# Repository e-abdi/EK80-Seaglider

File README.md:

# EK80 Seaglider

Integration of a Simrad EK80 echosounder on a Seaglider: mounting brackets and
the noise suppressor interface board.

## Mechanical

EK80 brackets on the glider ([STEP](Mechanical/EK80%20Brackets.step)).

## Noise suppressor PCB

Raspberry Pi Pico interface board between the glider and the EK80
([details](ek80%20noise%20suppressor/README.md)).

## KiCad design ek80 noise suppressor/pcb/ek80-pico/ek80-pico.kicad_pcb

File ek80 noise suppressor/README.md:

# EK80 noise suppressor V3.0 (Raspberry Pi Pico)

Interface board between a Seaglider and an EK80 echosounder: galvanically
isolated glider link, RS-422 to the EK80, an on-board pack with protection
and charger, and a latching relay that connects the pack either to the EK80 or
to the charger.

## Pin map

| Pico pin | GPIO | Net | Use |
|---|---|---|---|
| 21 / 22 | GP16 / GP17 | STX / SRX | UART0 to the EK80 (U1, J3) |
| 26 / 27 | GP20 / GP21 | GTX / GRX | UART1 to the glider (U5/U2, U4, J2) |
| 29 | GP22 | RELAY_SET | relay pulse: pack → charger |
| 32 | GP27 | RELAY_RESET | relay pulse: pack → EK80 |
| 31 | GP26 / ADC0 | VBAT_SENSE | pack voltage (10k / 2.4k) |
| 34 | GP28 | BMS_PRES | bq77915 PRES via JP2 |
| 24 / 25 | GP18 / GP19 | SDA / SCL | J6 (BQ76920), I2C1 |
| 19 / 20 | GP14 / GP15 | ALM / BOOT | J6 |
| 36 | 3V3 | SENSOR3.3V | supply in |
| 37 | 3V3_EN | PACK- | module regulator off |

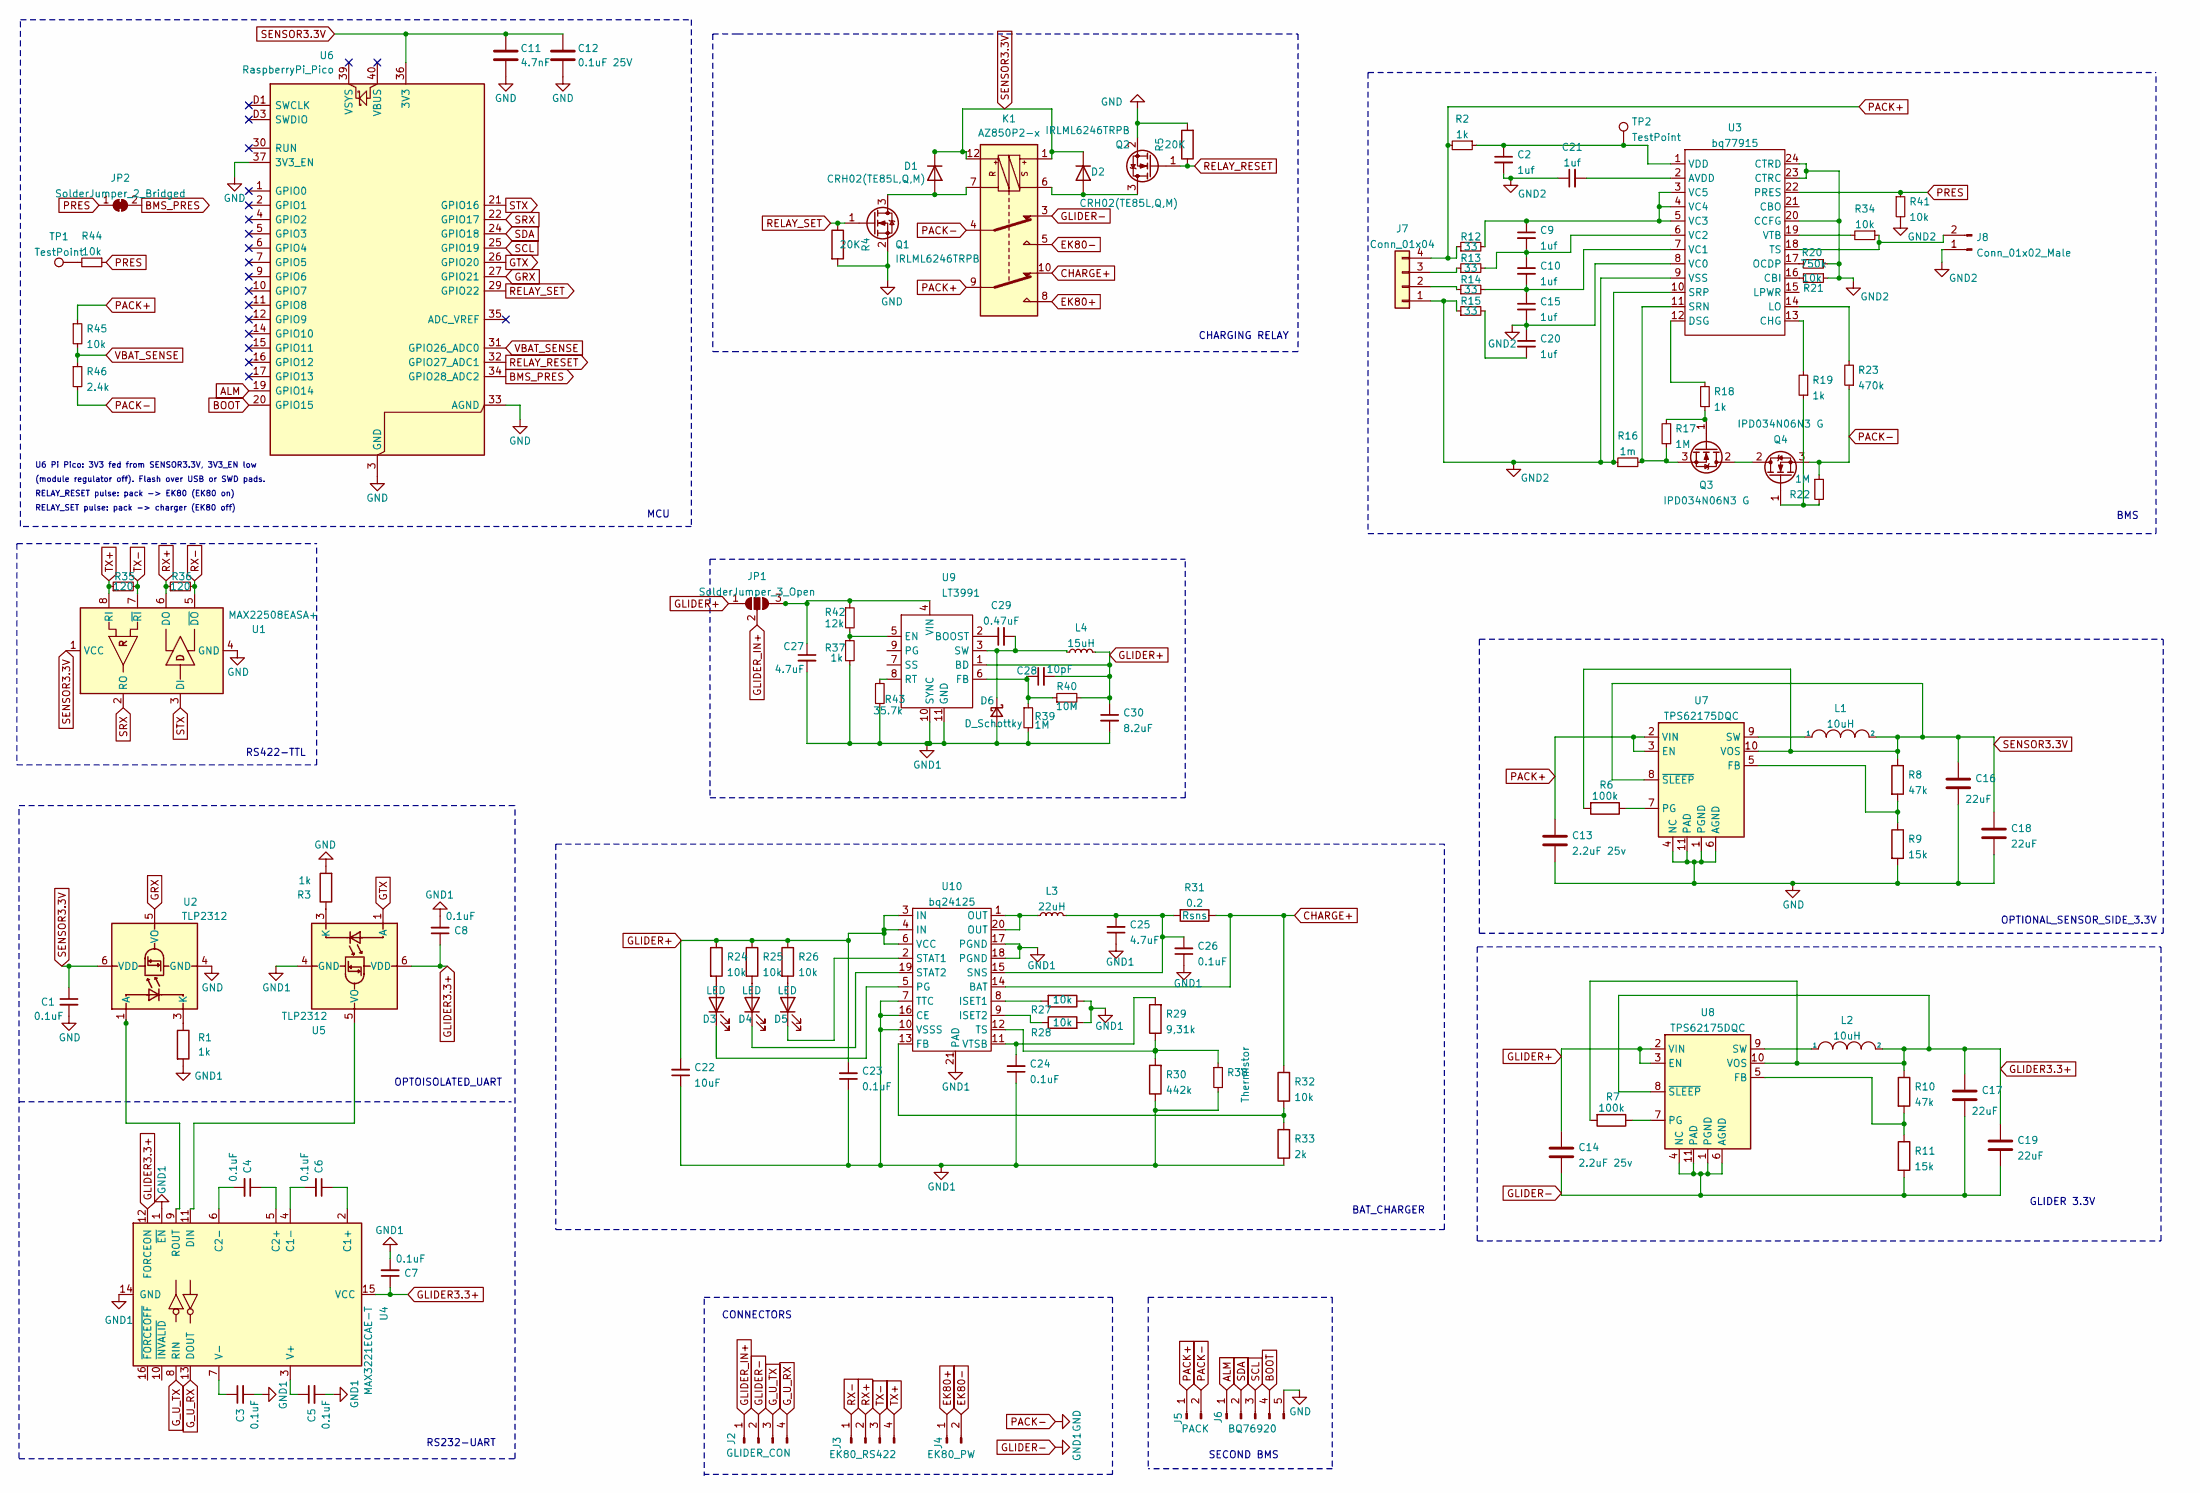
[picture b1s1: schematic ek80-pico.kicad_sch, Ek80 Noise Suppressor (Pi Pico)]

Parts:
C1, C3, C4, C5, C6, C7, C8, C23, C24, C26: 0.1uF; C_0402_1005Metric_Pad0.74x0.62mm_HandSolder
C2, C9, C10, C15, C20, C21: 1uf; C_0402_1005Metric_Pad0.74x0.62mm_HandSolder
C11: 4.7nF; C_0402_1005Metric_Pad0.74x0.62mm_HandSolder
C12: 0.1uF 25V; C_0402_1005Metric_Pad0.74x0.62mm_HandSolder
C13, C14: 2.2uF 25v; C_0805_2012Metric_Pad1.18x1.45mm_HandSolder
C16, C17, C18, C19: 22uF; C_0805_2012Metric_Pad1.18x1.45mm_HandSolder
C22: 10uF; C_0402_1005Metric_Pad0.74x0.62mm_HandSolder
C25, C27: 4.7uF; C_0603_1608Metric_Pad1.08x0.95mm_HandSolder
C28: 10pF; C_0805_2012Metric_Pad1.18x1.45mm_HandSolder
C29: 0.47uF; C_0402_1005Metric_Pad0.74x0.62mm_HandSolder
C30: 8.2uF; C_1210_3225Metric_Pad1.33x2.70mm_HandSolder
D1, D2: CRH02(TE85L,Q,M); D_SOD-123F
D3, D4, D5: LED; LED_0402_1005Metric_Pad0.77x0.64mm_HandSolder
D6: D_Schottky; D_TUMD2
J2: GLIDER_CON; PinHeader_1x04_P2.54mm_Vertical
J3: EK80_RS422; Stocko_MKS_1654-6-0-404_1x4_P2.50mm_Vertical
J4: EK80_PW; SolderWire-1.5sqmm_1x02_P6mm_D1.7mm_OD3mm
J5: PACK; SolderWire-1.5sqmm_1x02_P6mm_D1.7mm_OD3mm
J6: BQ76920; PinSocket_1x05_P2.00mm_Vertical
J7: Conn_01x04; JST_EH_B4B-EH-A_1x04_P2.50mm_Vertical
J8: Conn_01x02_Male; JST_EH_B2B-EH-A_1x02_P2.50mm_Vertical
JP1: SolderJumper_3_Open; SolderJumper-3_P1.3mm_Open_RoundedPad1.0x1.5mm
JP2: SolderJumper_2_Bridged; SolderJumper-2_P1.3mm_Bridged_RoundedPad1.0x1.5mm
K1: AZ850P2-x; Relay_DPDT_Kemet_EE2_NU_DoubleCoil
L1, L2: 10uH; L_Vishay_IFSC-1515AH_4x4x1.8mm
L3: 22uH; L_Vishay_IFSC-1515AH_4x4x1.8mm
L4: 15uH; L_TDK_SLF10145
Q1, Q2: IRLML6246TRPB; SOT-23
Q3, Q4: IPD034N06N3 G; TO-252-2
R1, R2, R3, R18, R19, R37: 1k; R_0603_1608Metric_Pad0.98x0.95mm_HandSolder
R4, R5: 20K; R_0402_1005Metric_Pad0.72x0.64mm_HandSolder
R6, R7: 100k; R_0603_1608Metric_Pad0.98x0.95mm_HandSolder
R8, R10: 47k; R_0603_1608Metric_Pad0.98x0.95mm_HandSolder
R9, R11: 15k; R_0603_1608Metric_Pad0.98x0.95mm_HandSolder
R12, R13, R14, R15: 33; R_0402_1005Metric_Pad0.72x0.64mm_HandSolder
R16: 1m; R_0612_1632Metric_Pad1.18x3.40mm_HandSolder
R17, R22, R39: 1M; R_0402_1005Metric_Pad0.72x0.64mm_HandSolder
R20: 750k; R_0402_1005Metric_Pad0.72x0.64mm_HandSolder
R21, R24, R25, R26, R27, R28, R32, R34, R41, R44, R45: 10k; R_0402_1005Metric_Pad0.72x0.64mm_HandSolder
R23: 470k; R_0402_1005Metric_Pad0.72x0.64mm_HandSolder
R29: 9,31k; R_0402_1005Metric_Pad0.72x0.64mm_HandSolder
R30: 442k; R_0402_1005Metric_Pad0.72x0.64mm_HandSolder
R31: 0.2; R_2512_6332Metric_Pad1.40x3.35mm_HandSolder
R33: 2k; R_0603_1608Metric_Pad0.98x0.95mm_HandSolder
R35, R36: 120; R_0402_1005Metric_Pad0.72x0.64mm_HandSolder
R38: Thermistor; R_Axial_DIN0204_L3.6mm_D1.6mm_P2.54mm_Vertical
R40: 10M; R_0402_1005Metric_Pad0.72x0.64mm_HandSolder
R42: 12k; R_0402_1005Metric_Pad0.72x0.64mm_HandSolder
R43: 35.7k; R_0402_1005Metric_Pad0.72x0.64mm_HandSolder
R46: 2.4k; R_0402_1005Metric_Pad0.72x0.64mm_HandSolder
TP1, TP2: TestPoint; TestPoint_Pad_D1.0mm
U1: MAX22508EASA+; SOIC-8_3.9x4.9mm_P1.27mm
U2, U5: TLP2312; SO-5_4.4x3.6mm_P1.27mm
U3: bq77915; TSSOP-24_4.4x7.8mm_P0.65mm
U4: MAX3221ECAE-T; SSOP-16_5.3x6.2mm_P0.65mm
U6: RaspberryPi_Pico; RaspberryPi_Pico_SMD_HandSolder
U7, U8: TPS62175DQC; WSON-10-1EP_2x3mm_P0.5mm_EP0.84x2.4mm_ThermalVias
U9: LT3991; MSOP-10-1EP_3x3mm_P0.5mm_EP1.68x1.88mm_ThermalVias
U10: bq24125; Texas_VQFN-RHL-20_ThermalVias

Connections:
ALM: J6.1, U6.19 (GPIO14)
BMS_PRES: JP2.2 (B), U6.34 (GPIO28_ADC2)
BOOT: J6.4, U6.20 (GPIO15)
CHARGE+: K1.10, R31.1, R32.2, U10.14 (BAT)
EK80+: J4.1, K1.8
EK80-: J4.2, K1.5
GLIDER3.3+: C7.1, C8.1, C17.1, C19.1, L2.2, R7.2, R10.1, U4.12 (FORCEON), U4.15 (VCC), U5.6 (VDD), U8.8 (~SLEEP), U8.10 (VOS)
GLIDER+: C14.1, C22.2, C23.2, C28.2, C30.1, JP1.1 (A), L4.2, R24.1, R25.1, R26.1, R40.2, U8.2 (VIN), U8.3 (EN), U9.1 (BD), U10.3 (IN), U10.4 (IN), U10.6 (VCC)
GLIDER-: C3.2, C5.2, C7.2, C8.2, C14.2, C17.2, C19.2, C22.1, C23.1, C24.1, C25.1, C26.1, C27.2, C30.2, D6.2 (A), J2.2, K1.3, R1.2, R11.2, R27.1, R28.2, R30.1, R33.1, R37.2, R38.2, R39.2, R43.2, U4.1 (~EN), U4.14 (GND), U5.4 (GND), U8.1 (PGND), U8.4 (NC), U8.6 (AGND), U8.11 (PAD), U9.10 (SYNC), U9.11 (GND), U10.7 (TTC), U10.10 (VSSS), U10.16 (CE), U10.17 (PGND), U10.18 (PGND), U10.21 (PAD)
GLIDER_IN+: J2.1, JP1.2 (C)
GND2: C2.2, C15.2, C20.1, C21.1, J7.1, J8.1, R15.1, R16.1, R20.1, R21.1, R41.2, U3.8 (VC0), U3.9 (VSS), U3.10 (SRP), U3.20 (CCFG), U3.23 (CTRC), U3.24 (CTRD)
GRX: U2.5 (VO), U6.27 (GPIO21)
GTX: U5.1 (A), U6.26 (GPIO20)
G_U_RX: J2.4, U4.13 (DOUT)
G_U_TX: J2.3, U4.8 (RIN)
unnamed: C20.2, R15.2
unnamed: D1.2 (A), K1.7, Q1.3 (D)
unnamed: D2.2 (A), K1.6, Q2.3 (D)
unnamed: D3.2 (A), R24.2
unnamed: D3.1 (K), U10.5 (PG)
unnamed: D4.2 (A), R25.2
unnamed: D4.1 (K), U10.19 (STAT2)
unnamed: D5.2 (A), R26.2
unnamed: D5.1 (K), U10.2 (STAT1)
unnamed: C29.2, D6.1 (K), L4.1, U9.3 (SW)
unnamed: J7.2, R14.1
unnamed: J7.3, R13.1
unnamed: J8.2, R34.1, U3.18 (TS)
unnamed: C27.1, JP1.3 (B), R42.1, U9.4 (VIN)
unnamed: L3.1, U10.1 (OUT), U10.20 (OUT)
unnamed: Q3.2 (D), Q4.2 (D)
unnamed: Q3.1 (G), R17.2, R18.1
unnamed: Q3.3 (S), R16.2, R17.1, U3.11 (SRN)
unnamed: Q4.1 (G), R19.1, R22.2
unnamed: R44.2, TP1.1
unnamed: U2.1 (A), U4.9 (ROUT)
unnamed: R1.1, U2.3 (K)
unnamed: C21.2, U3.2 (AVDD)
unnamed: R21.2, U3.16 (CBI)
unnamed: R19.2, U3.13 (CHG)
unnamed: R18.2, U3.12 (DSG)
unnamed: R23.2, U3.14 (LO)
unnamed: R20.2, U3.17 (OCDP)
unnamed: C10.2, C15.1, R14.2, U3.7 (VC1)
unnamed: C9.2, C10.1, R13.2, U3.6 (VC2)
unnamed: C9.1, R12.2, U3.3 (VC5), U3.4 (VC4), U3.5 (VC3)
unnamed: C2.1, R2.1, TP2.1, U3.1 (VDD)
unnamed: R34.2, U3.19 (VTB)
unnamed: C6.1, U4.2 (C1+)
unnamed: C6.2, U4.4 (C1-)
unnamed: C4.1, U4.5 (C2+)
unnamed: C4.2, U4.6 (C2-)
unnamed: U4.11 (DIN), U5.5 (VO)
unnamed: C5.1, U4.3 (V+)
unnamed: C3.1, U4.7 (V-)
unnamed: R3.1, U5.3 (K)
unnamed: R8.2, R9.1, U7.5 (FB)
unnamed: R6.1, U7.7 (PG)
unnamed: L1.1, U7.9 (SW)
unnamed: R10.2, R11.1, U8.5 (FB)
unnamed: R7.1, U8.7 (PG)
unnamed: L2.1, U8.9 (SW)
unnamed: C29.1, U9.2 (BOOST)
unnamed: R37.1, R42.2, U9.5 (EN)
unnamed: C28.1, R39.1, R40.1, U9.6 (FB)
unnamed: R43.1, U9.8 (RT)
unnamed: R32.1, R33.2, U10.13 (FB)
unnamed: R27.2, U10.8 (ISET1)
unnamed: R28.1, U10.9 (ISET2)
unnamed: C25.2, C26.2, L3.2, R31.2, U10.15 (SNS)
unnamed: R29.1, R30.2, R38.1, U10.12 (TS)
unnamed: C24.2, R29.2, U10.11 (VTSB)
PACK+: C13.1, J5.1, J7.4, K1.9, R2.2, R12.1, R45.1, U7.2 (VIN), U7.3 (EN)
PACK-: C1.2, C11.2, C12.2, C13.2, C16.2, C18.2, J5.2, J6.5, K1.4, Q1.2 (S), Q2.2 (S), Q4.3 (S), R3.2, R4.2, R5.2, R9.2, R22.1, R23.1, R46.2, U1.4 (GND), U2.4 (GND), U6.3 (GND), U6.8 (GND), U6.13 (GND), U6.18 (GND), U6.23 (GND), U6.28 (GND), U6.33 (AGND), U6.37 (3V3_EN), U6.38 (GND), U6.D2 (GND), U7.1 (PGND), U7.4 (NC), U7.6 (AGND), U7.11 (PAD)
PRES: JP2.1 (A), R41.1, R44.1, U3.22 (PRES)
RELAY_RESET: Q2.1 (G), R5.1, U6.32 (GPIO27_ADC1)
RELAY_SET: Q1.1 (G), R4.1, U6.29 (GPIO22)
RX+: J3.2, R36.1, U1.6 (DO)
RX-: J3.1, R36.2, U1.5 (~DO)
SCL: J6.3, U6.25 (GPIO19)
SDA: J6.2, U6.24 (GPIO18)
SENSOR3.3V: C1.1, C11.1, C12.1, C16.1, C18.1, D1.1 (K), D2.1 (K), K1.1, K1.12, L1.2, R6.2, R8.1, U1.1 (VCC), U2.6 (VDD), U6.36 (3V3), U7.8 (~SLEEP), U7.10 (VOS)
SRX: U1.2 (RO), U6.22 (GPIO17)
STX: U1.3 (DI), U6.21 (GPIO16)
TX+: J3.4, R35.1, U1.8 (RI)
TX-: J3.3, R35.2, U1.7 (~RI)
VBAT_SENSE: R45.2, R46.1, U6.31 (GPIO26_ADC0)

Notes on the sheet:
OPTOISOLATED_UART
BAT_CHARGER
CHARGING RELAY
CONNECTORS
RS422-TTL
OPTIONAL_SENSOR_SIDE_3.3V
BMS
GLIDER 3.3V
SECOND BMS
RS232-UART
MCU
U6 Pi Pico: 3V3 fed from SENSOR3.3V, 3V3_EN low
(module regulator off). Flash over USB or SWD pads.
RELAY_RESET pulse: pack -> EK80 (EK80 on)
RELAY_SET pulse: pack -> charger (EK80 off)

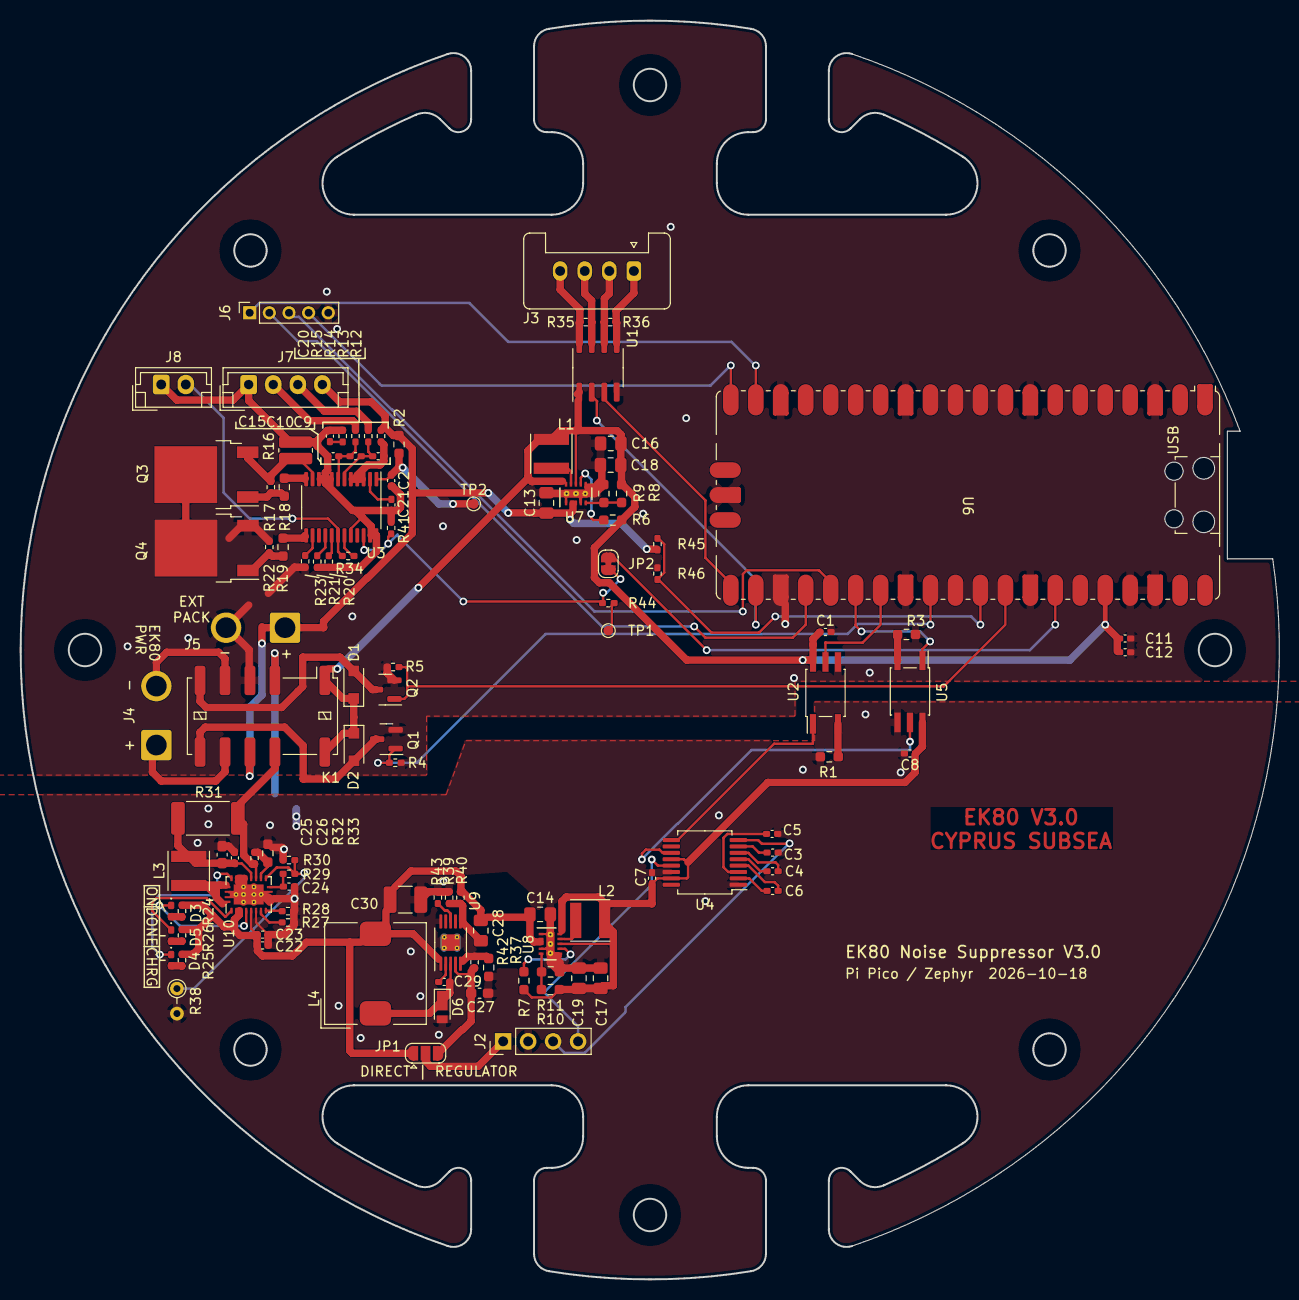
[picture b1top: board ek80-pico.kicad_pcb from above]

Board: 2 copper layers, 128.1 x 128.1 mm, 112 parts (0 on the bottom side), 87 nets.

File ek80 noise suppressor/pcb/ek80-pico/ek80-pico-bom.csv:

"Reference","Value","Footprint","QUANTITY"
"C1,C3-C8,C23,C24,C26","0.1uF","Capacitor_SMD:C_0402_1005Metric_Pad0.74x0.62mm_HandSolder","10"
"C2,C9,C10,C15,C20,C21","1uf","Capacitor_SMD:C_0402_1005Metric_Pad0.74x0.62mm_HandSolder","6"
"C11","4.7nF","Capacitor_SMD:C_0402_1005Metric_Pad0.74x0.62mm_HandSolder","1"
"C12","0.1uF 25V","Capacitor_SMD:C_0402_1005Metric_Pad0.74x0.62mm_HandSolder","1"
"C13,C14","2.2uF 25v","Capacitor_SMD:C_0805_2012Metric_Pad1.18x1.45mm_HandSolder","2"
"C16-C19","22uF","Capacitor_SMD:C_0805_2012Metric_Pad1.18x1.45mm_HandSolder","4"
"C22","10uF","Capacitor_SMD:C_0402_1005Metric_Pad0.74x0.62mm_HandSolder","1"
"C25,C27","4.7uF","Capacitor_SMD:C_0603_1608Metric_Pad1.08x0.95mm_HandSolder","2"
"C28","10pF","Capacitor_SMD:C_0805_2012Metric_Pad1.18x1.45mm_HandSolder","1"
"C29","0.47uF","Capacitor_SMD:C_0402_1005Metric_Pad0.74x0.62mm_HandSolder","1"
"C30","8.2uF","Capacitor_SMD:C_1210_3225Metric_Pad1.33x2.70mm_HandSolder","1"
"D1,D2","CRH02(TE85L,Q,M)","Diode_SMD:D_SOD-123F","2"
"D3-D5","LED","LED_SMD:LED_0402_1005Metric_Pad0.77x0.64mm_HandSolder","3"
"D6","D_Schottky","Diode_SMD:D_TUMD2","1"
"J2","GLIDER_CON","Connector_PinHeader_2.54mm:PinHeader_1x04_P2.54mm_Vertical","1"
"J3","EK80_RS422","Connector_Stocko:Stocko_MKS_1654-6-0-404_1x4_P2.50mm_Vertical","1"
"J4","EK80_PW","Connector_Wire:SolderWire-1.5sqmm_1x02_P6mm_D1.7mm_OD3mm","1"
"J5","PACK","Connector_Wire:SolderWire-1.5sqmm_1x02_P6mm_D1.7mm_OD3mm","1"
"J6","BQ76920","Connector_PinSocket_2.00mm:PinSocket_1x05_P2.00mm_Vertical","1"
"J7","Conn_01x04","Connector_JST:JST_EH_B4B-EH-A_1x04_P2.50mm_Vertical","1"
"J8","Conn_01x02_Male","Connector_JST:JST_EH_B2B-EH-A_1x02_P2.50mm_Vertical","1"
"JP1","SolderJumper_3_Open","Jumper:SolderJumper-3_P1.3mm_Open_RoundedPad1.0x1.5mm","1"
"JP2","SolderJumper_2_Bridged","Jumper:SolderJumper-2_P1.3mm_Bridged_RoundedPad1.0x1.5mm","1"
"K1","AZ850P2-x","Relay_SMD:Relay_DPDT_Kemet_EE2_NU_DoubleCoil","1"
"L1,L2","10uH","Inductor_SMD:L_Vishay_IFSC-1515AH_4x4x1.8mm","2"
"L3","22uH","Inductor_SMD:L_Vishay_IFSC-1515AH_4x4x1.8mm","1"
"L4","15uH","Inductor_SMD:L_TDK_SLF10145","1"
"Q1,Q2","IRLML6246TRPB","Package_TO_SOT_SMD:SOT-23","2"
"Q3,Q4","IPD034N06N3 G","Package_TO_SOT_SMD:TO-252-2","2"
"R1-R3,R18,R19,R37","1k","Resistor_SMD:R_0603_1608Metric_Pad0.98x0.95mm_HandSolder","6"
"R4,R5","20K","Resistor_SMD:R_0402_1005Metric_Pad0.72x0.64mm_HandSolder","2"
"R6,R7","100k","Resistor_SMD:R_0603_1608Metric_Pad0.98x0.95mm_HandSolder","2"
"R8,R10","47k","Resistor_SMD:R_0603_1608Metric_Pad0.98x0.95mm_HandSolder","2"
"R9,R11","15k","Resistor_SMD:R_0603_1608Metric_Pad0.98x0.95mm_HandSolder","2"
"R12-R15","33","Resistor_SMD:R_0402_1005Metric_Pad0.72x0.64mm_HandSolder","4"
"R16","1m","Resistor_SMD:R_0612_1632Metric_Pad1.18x3.40mm_HandSolder","1"
"R17,R22,R39","1M","Resistor_SMD:R_0402_1005Metric_Pad0.72x0.64mm_HandSolder","3"
"R20","750k","Resistor_SMD:R_0402_1005Metric_Pad0.72x0.64mm_HandSolder","1"
"R21,R24-R28,R32,R34,R41,R44,R45","10k","Resistor_SMD:R_0402_1005Metric_Pad0.72x0.64mm_HandSolder","11"
"R23","470k","Resistor_SMD:R_0402_1005Metric_Pad0.72x0.64mm_HandSolder","1"
"R29","9,31k","Resistor_SMD:R_0402_1005Metric_Pad0.72x0.64mm_HandSolder","1"
"R30","442k","Resistor_SMD:R_0402_1005Metric_Pad0.72x0.64mm_HandSolder","1"
"R31","0.2","Resistor_SMD:R_2512_6332Metric_Pad1.40x3.35mm_HandSolder","1"
"R33","2k","Resistor_SMD:R_0603_1608Metric_Pad0.98x0.95mm_HandSolder","1"
"R35,R36","120","Resistor_SMD:R_0402_1005Metric_Pad0.72x0.64mm_HandSolder","2"
"R38","Thermistor","Resistor_THT:R_Axial_DIN0204_L3.6mm_D1.6mm_P2.54mm_Vertical","1"
"R40","10M","Resistor_SMD:R_0402_1005Metric_Pad0.72x0.64mm_HandSolder","1"
"R42","12k","Resistor_SMD:R_0402_1005Metric_Pad0.72x0.64mm_HandSolder","1"
"R43","35.7k","Resistor_SMD:R_0402_1005Metric_Pad0.72x0.64mm_HandSolder","1"
"R46","2.4k","Resistor_SMD:R_0402_1005Metric_Pad0.72x0.64mm_HandSolder","1"
"TP1,TP2","TestPoint","TestPoint:TestPoint_Pad_D1.0mm","2"
"U1","MAX22508EASA+","Package_SO:SOIC-8_3.9x4.9mm_P1.27mm","1"
"U2,U5","TLP2312","Package_SO:SO-5_4.4x3.6mm_P1.27mm","2"
"U3","bq77915","Package_SO:TSSOP-24_4.4x7.8mm_P0.65mm","1"
"U4","MAX3221ECAE-T","Package_SO:SSOP-16_5.3x6.2mm_P0.65mm","1"
"U6","RaspberryPi_Pico","Module:RaspberryPi_Pico_SMD_HandSolder","1"
"U7,U8","TPS62175DQC","Package_SON:WSON-10-1EP_2x3mm_P0.5mm_EP0.84x2.4mm_ThermalVias","2"
"U9","LT3991","Package_SO:MSOP-10-1EP_3x3mm_P0.5mm_EP1.68x1.88mm_ThermalVias","1"
"U10","bq24125","Package_DFN_QFN:Texas_VQFN-RHL-20_ThermalVias","1"
